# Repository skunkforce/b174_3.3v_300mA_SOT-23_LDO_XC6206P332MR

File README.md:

# edgy_board number b174
This design is part of the [edgy board project](https://github.com/skunkforce/edgy_boards). It provides a 300mA 3.3V LDO

# getting started
This repository uses submodules. After cloning use the command 

```$ git submodule update --init --recursive```

to pull the submodules before opening the project with kicad. 

# Tests
Tests can be found in [TESTS.md](TESTS.md)

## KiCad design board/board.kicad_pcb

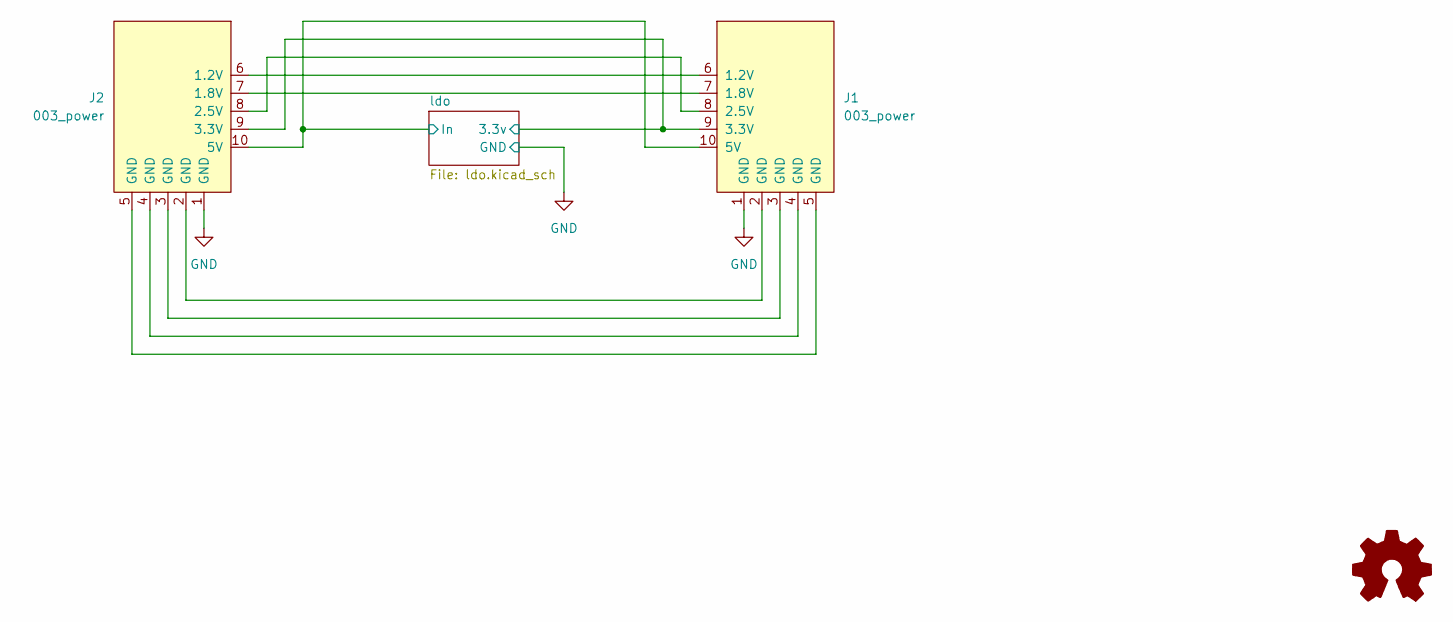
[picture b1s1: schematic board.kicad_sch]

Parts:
J1: 003_power; on_edge_2x05_host
J2: 003_power; on_edge_2x05_device
LOGO1: Logo_Open_Hardware_Small; OSHW-Symbol_6.7x6mm_SilkScreen

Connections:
/ldo/3.3v: J1.9 (3.3V), J2.9 (3.3V); also elsewhere on the board
/ldo/In: J1.10 (5V), J2.10 (5V); also elsewhere on the board
GND: J1.1 (GND), J2.1 (GND); also elsewhere on the board
unnamed: J1.6 (1.2V), J2.6 (1.2V)
unnamed: J1.7 (1.8V), J2.7 (1.8V)
unnamed: J1.8 (2.5V), J2.8 (2.5V)
unnamed: J1.2 (GND), J2.2 (GND)
unnamed: J1.3 (GND), J2.3 (GND)
unnamed: J1.4 (GND), J2.4 (GND)
unnamed: J1.5 (GND), J2.5 (GND)

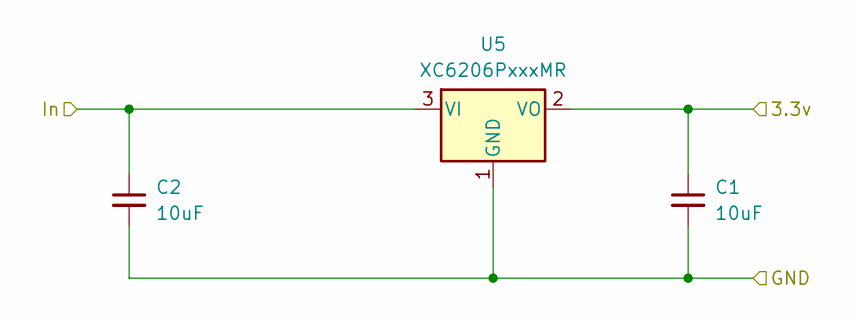
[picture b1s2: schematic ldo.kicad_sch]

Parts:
C1, C2: 10uF; C_0603_1608Metric; lcsc C19702
U5: XC6206PxxxMR; SOT-23-3; lcsc C5148692

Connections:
/ldo/3.3v: C1.1, U5.2 (VO); also elsewhere on the board
/ldo/In: C2.1, U5.3 (VI); also elsewhere on the board
GND: C1.2, C2.2, U5.1 (GND); also elsewhere on the board

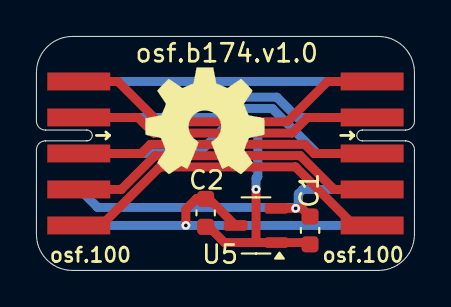
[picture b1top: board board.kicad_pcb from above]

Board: 2 copper layers, 21.0 x 13.0 mm, 6 parts (0 on the bottom side), 10 nets.

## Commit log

2024-01-15 added silkscreen and jlc
2025-07-26 V1.0
